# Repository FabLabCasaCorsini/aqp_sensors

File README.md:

# aqp_sensors
Software components for the Aquaponic project - Forked in Casa Corsini github

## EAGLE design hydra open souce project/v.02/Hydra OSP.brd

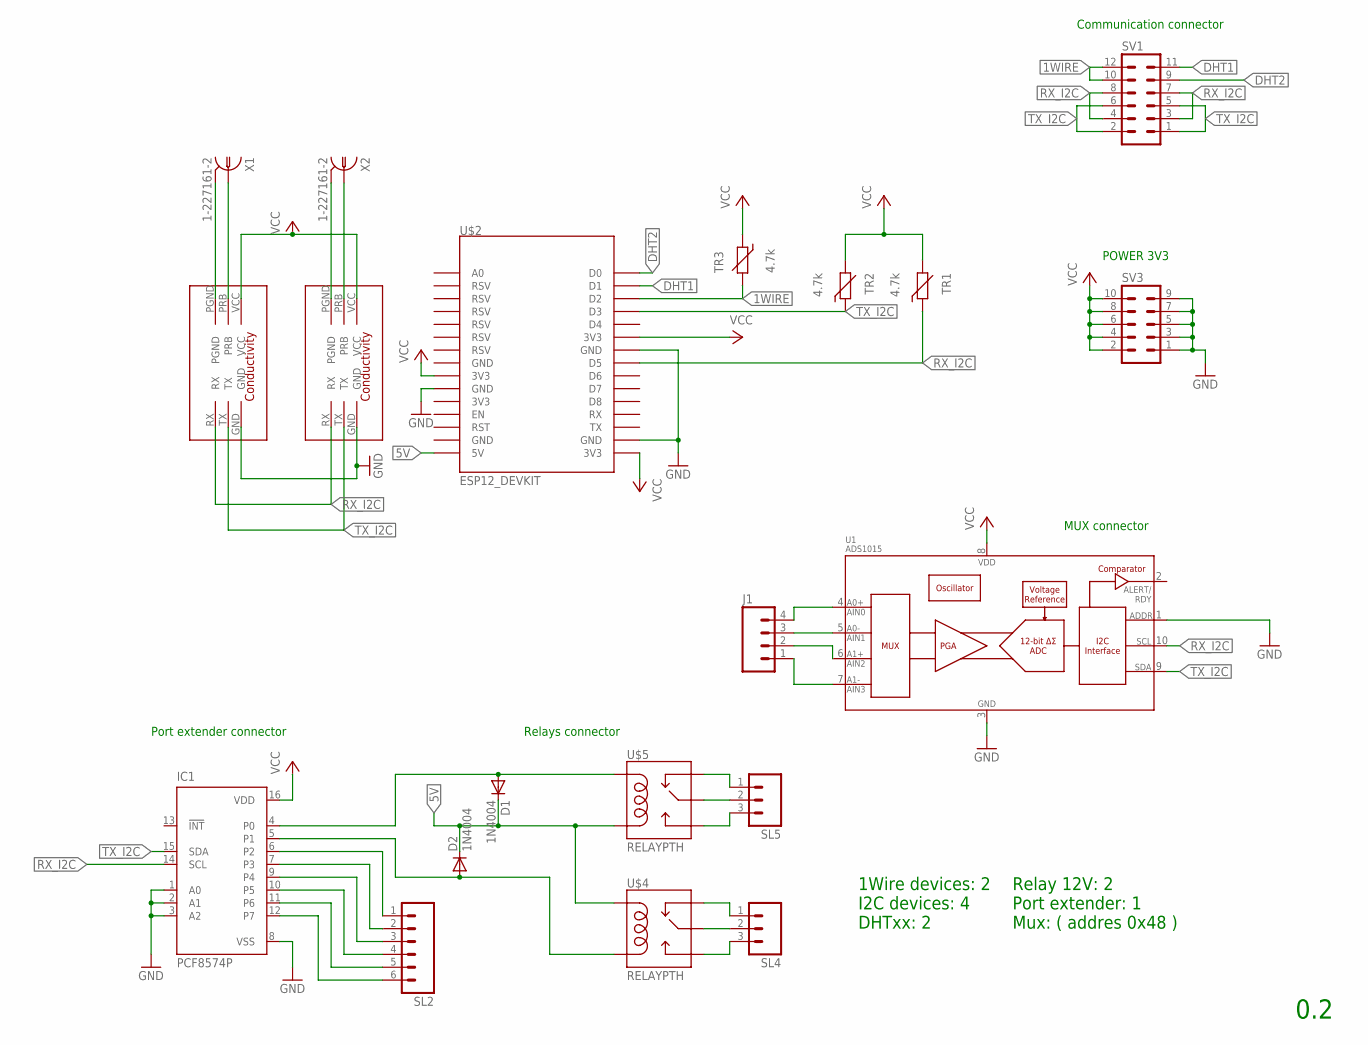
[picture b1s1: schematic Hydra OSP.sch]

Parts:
D1, D2: 1N4004; DO41-10
IC1: PCF8574P; DIL16
J1: M04LOCK; 1X04_LOCK
SL2: M06; 06P
SL4, SL5: M03; 03P
SV1: MA06-2
SV3: MA05-2
TR1, TR2, TR3: 4.7k; R-5
U1: ADS1015; MSOP10
U$1, U$3: ATLSCI_COND; ATLAS_SCI_COND
U$2: ESP12_DEVKIT
U$4, U$5: RELAYPTH; SRD-05VDC-SL-C
X1, X2: 1-227161-2; AMP_227161

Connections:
1WIRE: SV1.10, SV1.12, TR3.2, U$2.D2
5V: D1.C, D2.C, U$2.5V, U$4.COIL1, U$5.COIL0
DHT1: SV1.11, U$2.D1
DHT2: SV1.9, U$2.D0
GND: IC1.1 (A0), IC1.2 (A1), IC1.3 (A2), IC1.8 (VSS), SV3.1, SV3.3, SV3.5, SV3.7, SV3.9, U1.1 (ADDR), U1.3 (VSS), U$1.GND, U$2.GND@0 (GND), U$2.GND@2 (GND), U$2.GND@3 (GND), U$3.GND
unnamed: U$1.PGND, X1.2
unnamed: U$1.PRB, X1.1
unnamed: U$3.PRB, X2.1
unnamed: U$3.PGND, X2.2
unnamed: D1.A, IC1.4 (P0), U$5.COIL1
unnamed: D2.A, IC1.5 (P1), U$4.COIL0
unnamed: SL4.1, U$4.SWCLOSED (SWCLOSE)
unnamed: SL4.2, U$4.SWCOMMON
unnamed: J1.4, U1.4 (AIN0)
unnamed: J1.3, U1.5 (AIN1)
unnamed: J1.2, U1.6 (AIN2)
unnamed: J1.1, U1.7 (AIN3)
unnamed: IC1.6 (P2), SL2.1
unnamed: IC1.7 (P3), SL2.2
unnamed: IC1.9 (P4), SL2.3
unnamed: IC1.10 (P5), SL2.4
unnamed: IC1.11 (P6), SL2.5
unnamed: IC1.12 (P7), SL2.6
unnamed: SL4.3, U$4.SWOPEN
unnamed: SL5.1, U$5.SWCLOSED (SWCLOSE)
unnamed: SL5.2, U$5.SWCOMMON
unnamed: SL5.3, U$5.SWOPEN
RX_I2C: IC1.14 (SCL), SV1.3, SV1.4, SV1.7, SV1.8, TR1.1, U1.10 (SCL), U$1.RX, U$2.D5, U$3.RX
TX_I2C: IC1.15 (SDA), SV1.1, SV1.2, SV1.5, SV1.6, TR2.1, U1.9 (SDA), U$1.TX, U$2.D3, U$3.TX
VCC: IC1.16 (VDD), SV3.2, SV3.4, SV3.6, SV3.8, SV3.10, TR1.2, TR2.2, TR3.1, U1.8 (VDD), U$1.VCC, U$2.3V3@1 (3V3), U$2.3V3@2 (3V3), U$2.3V3@3 (3V3), U$3.VCC

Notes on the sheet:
1Wire devices: 2 I2C devices: 4 DHTxx: 2
0.2
POWER 3V3
Communication connector
Port extender connector
Relays connector
Relay 12V: 2 Port extender: 1 Mux: ( addres 0x48 )
MUX connector

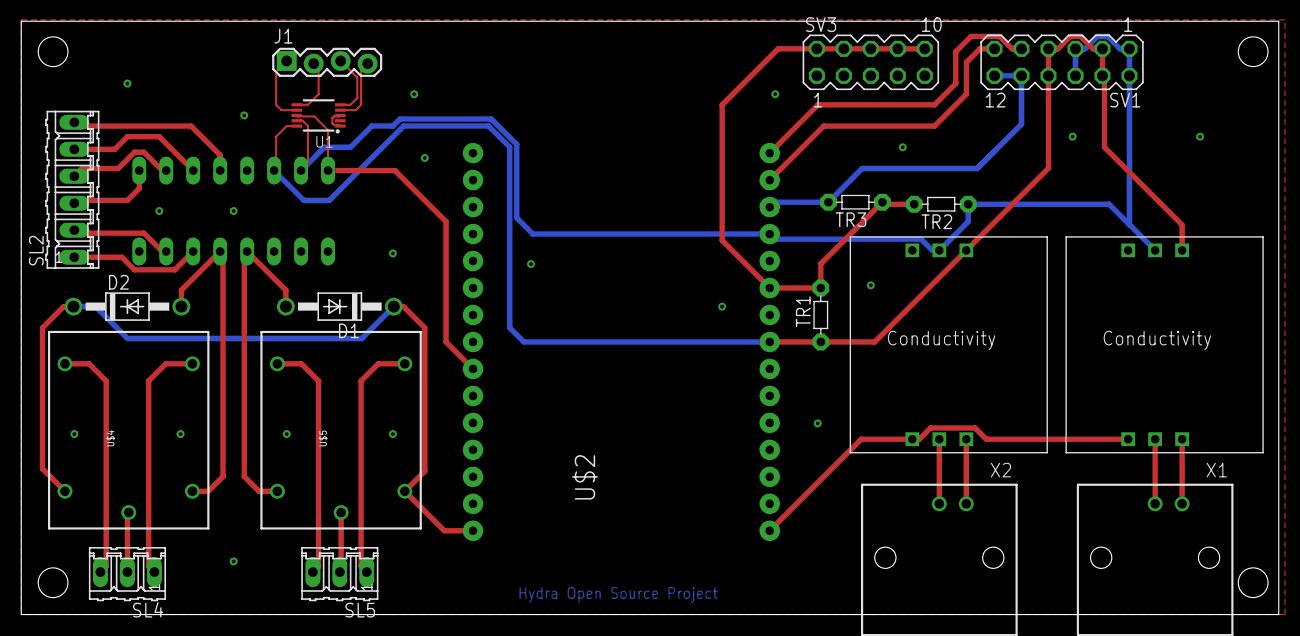
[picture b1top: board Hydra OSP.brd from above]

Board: 2 copper layers, 118.4 x 55.9 mm, 20 parts (1 on the bottom side), 30 nets.

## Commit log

2017-07-12 pcb v02
2018-01-24 WiFi manager
    This version is acutely on the PCB board.
2018-02-05 Fixed new version of OneWire libray
2018-02-08 Code ready for final test with Thingsboard
2018-02-12 New calibration parameters for pH

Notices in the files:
parts and their libraries:
SparkFun-AnalogIC: Licensing:Creative Commons ShareAlike 4.0 International - https://creativecommons.org/licenses/by-sa/4.0
